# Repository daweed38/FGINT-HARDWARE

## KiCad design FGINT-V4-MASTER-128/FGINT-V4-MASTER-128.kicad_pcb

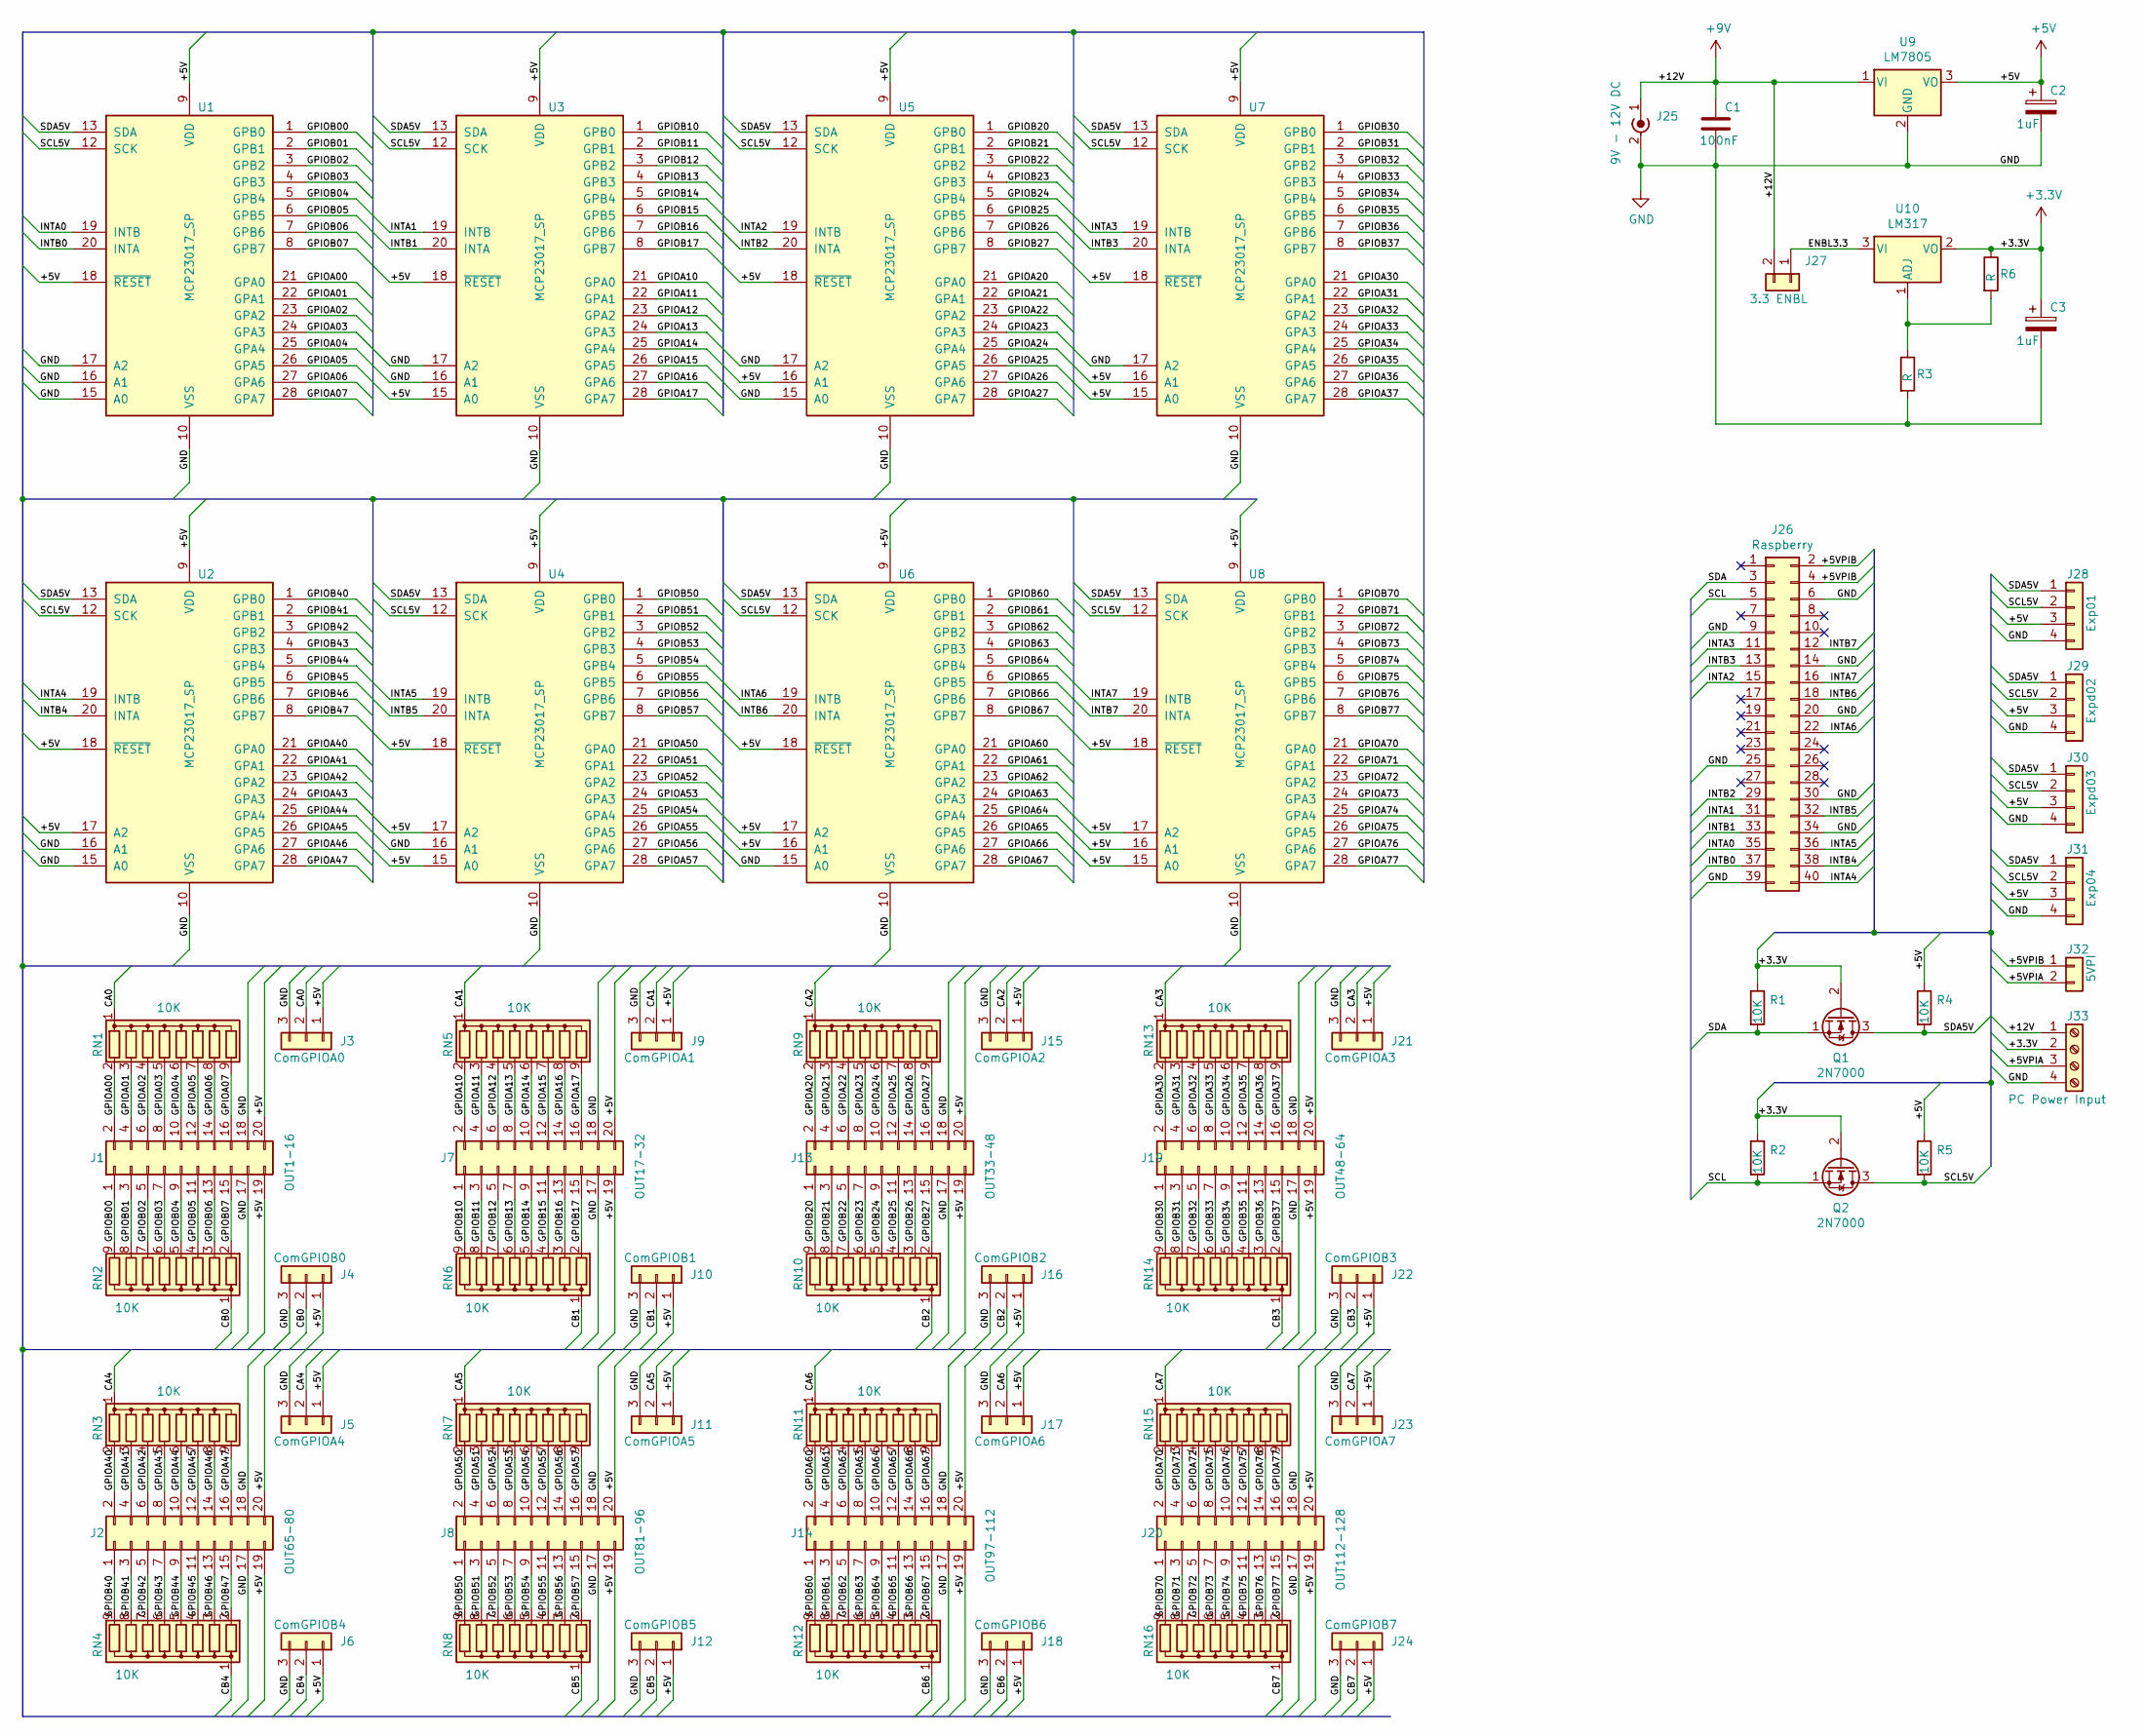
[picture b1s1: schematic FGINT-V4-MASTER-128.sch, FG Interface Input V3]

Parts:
C1: 100nF; C_Rect_L7.0mm_W2.5mm_P5.00mm
C2, C3: 1uF; CP_Radial_D5.0mm_P2.50mm
J1: OUT1-16; IDC-Header_2x10_P2.54mm_Horizontal
J2: OUT65-80; IDC-Header_2x10_P2.54mm_Horizontal
J3: ComGPIOA0; PinHeader_1x03_P2.54mm_Vertical
J4: ComGPIOB0; PinHeader_1x03_P2.54mm_Vertical
J5: ComGPIOA4; PinHeader_1x03_P2.54mm_Vertical
J6: ComGPIOB4; PinHeader_1x03_P2.54mm_Vertical
J7: OUT17-32; IDC-Header_2x10_P2.54mm_Horizontal
J8: OUT81-96; IDC-Header_2x10_P2.54mm_Horizontal
J9: ComGPIOA1; PinHeader_1x03_P2.54mm_Vertical
J10: ComGPIOB1; PinHeader_1x03_P2.54mm_Vertical
J11: ComGPIOA5; PinHeader_1x03_P2.54mm_Vertical
J12: ComGPIOB5; PinHeader_1x03_P2.54mm_Vertical
J13: OUT33-48; IDC-Header_2x10_P2.54mm_Horizontal
J14: OUT97-112; IDC-Header_2x10_P2.54mm_Horizontal
J15: ComGPIOA2; PinHeader_1x03_P2.54mm_Vertical
J16: ComGPIOB2; PinHeader_1x03_P2.54mm_Vertical
J17: ComGPIOA6; PinHeader_1x03_P2.54mm_Vertical
J18: ComGPIOB6; PinHeader_1x03_P2.54mm_Vertical
J19: OUT48-64; IDC-Header_2x10_P2.54mm_Horizontal
J20: OUT112-128; IDC-Header_2x10_P2.54mm_Horizontal
J21: ComGPIOA3; PinHeader_1x03_P2.54mm_Vertical
J22: ComGPIOB3; PinHeader_1x03_P2.54mm_Vertical
J23: ComGPIOA7; PinHeader_1x03_P2.54mm_Vertical
J24: ComGPIOB7; PinHeader_1x03_P2.54mm_Vertical
J25: 9V - 12V DC; BarrelJack_CUI_PJ-102AH_Horizontal
J26: Raspberry; IDC-Header_2x20_P2.54mm_Vertical
J27: 3.3 ENBL; PinHeader_1x02_P2.54mm_Vertical
J28: Exp01; Molex_KK-254_AE-6410-04A_1x04_P2.54mm_Vertical
J29: Expd02; Molex_KK-254_AE-6410-04A_1x04_P2.54mm_Vertical
J30: Expd03; Molex_KK-254_AE-6410-04A_1x04_P2.54mm_Vertical
J31: Exp04; Molex_KK-254_AE-6410-04A_1x04_P2.54mm_Vertical
J32: 5VPI; PinHeader_1x02_P2.54mm_Vertical
J33: PC Power Input; TerminalBlock_bornier-4_P5.08mm
Q1, Q2: 2N7000; TO-92_Inline
R1, R2, R4, R5: 10K; R_Axial_DIN0207_L6.3mm_D2.5mm_P7.62mm_Horizontal
R3, R6: R; R_Axial_DIN0207_L6.3mm_D2.5mm_P7.62mm_Horizontal
RN1, RN2, RN3, RN4, RN5, RN6, RN7, RN8, RN9, RN10, RN11, RN12, RN13, RN14, RN15, RN16: 10K; R_Array_SIP9
U1, U2, U3, U4, U5, U6, U7, U8: MCP23017_SP; DIP-28_W7.62mm
U9: LM7805; TO-220-3_Horizontal_TabDown
U10: LM317; TO-220-3_Horizontal_TabDown

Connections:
+3V3: C3.1, J33.2, Q1.2 (G), Q2.2 (G), R1.1, R2.1, R6.1, U10.2 (VO)
+5V: C2.1, J1.19, J1.20, J2.19, J2.20, J3.1, J4.1, J5.1, J6.1, J7.19, J7.20, J8.19, J8.20, J9.1, J10.1, J11.1, J12.1, J13.19, J13.20, J14.19, J14.20, J15.1, J16.1, J17.1, J18.1, J19.19, J19.20, J20.19, J20.20, J21.1, J22.1, J23.1, J24.1, J28.3, J29.3, J30.3, J31.3, R4.1, R5.1, U1.9 (VDD), U1.18 (~RESET~), U2.9 (VDD), U2.17 (A2), U2.18 (~RESET~), U3.9 (VDD), U3.15 (A0), U3.18 (~RESET~), U4.9 (VDD), U4.15 (A0), U4.17 (A2), U4.18 (~RESET~), U5.9 (VDD), U5.16 (A1), U5.18 (~RESET~), U6.9 (VDD), U6.16 (A1), U6.17 (A2), U6.18 (~RESET~), U7.9 (VDD), U7.15 (A0), U7.16 (A1), U7.18 (~RESET~), U8.9 (VDD), U8.15 (A0), U8.16 (A1), U8.17 (A2), U8.18 (~RESET~), U9.3 (VO)
+9V: C1.1, J25.1 (In), J27.2, J33.1, U9.1 (VI)
/+5VPIA: J32.2, J33.3
/+5VPIB: J26.2, J26.4, J32.1
/CA0: J3.2, RN1.1 (common)
/CA1: J9.2, RN5.1 (common)
/CA2: J15.2, RN9.1 (common)
/CA3: J21.2, RN13.1 (common)
/CA4: J5.2, RN3.1 (common)
/CA5: J11.2, RN7.1 (common)
/CA6: J17.2, RN11.1 (common)
/CA7: J23.2, RN15.1 (common)
/CB0: J4.2, RN2.1 (common)
/CB1: J10.2, RN6.1 (common)
/CB2: J16.2, RN10.1 (common)
/CB3: J22.2, RN14.1 (common)
/CB4: J6.2, RN4.1 (common)
/CB5: J12.2, RN8.1 (common)
/CB6: J18.2, RN12.1 (common)
/CB7: J24.2, RN16.1 (common)
/ENBL3.3: J27.1, U10.3 (VI)
/GPIOA00: J1.2, RN1.2 (R1), U1.21 (GPA0)
/GPIOA01: J1.4, RN1.3 (R2), U1.22 (GPA1)
/GPIOA02: J1.6, RN1.4 (R3), U1.23 (GPA2)
/GPIOA03: J1.8, RN1.5 (R4), U1.24 (GPA3)
/GPIOA04: J1.10, RN1.6 (R5), U1.25 (GPA4)
/GPIOA05: J1.12, RN1.7 (R6), U1.26 (GPA5)
/GPIOA06: J1.14, RN1.8 (R7), U1.27 (GPA6)
/GPIOA07: J1.16, RN1.9 (R8), U1.28 (GPA7)
/GPIOA10: J7.2, RN5.2 (R1), U3.21 (GPA0)
/GPIOA11: J7.4, RN5.3 (R2), U3.22 (GPA1)
/GPIOA12: J7.6, RN5.4 (R3), U3.23 (GPA2)
/GPIOA13: J7.8, RN5.5 (R4), U3.24 (GPA3)
/GPIOA14: J7.10, RN5.6 (R5), U3.25 (GPA4)
/GPIOA15: J7.12, RN5.7 (R6), U3.26 (GPA5)
/GPIOA16: J7.14, RN5.8 (R7), U3.27 (GPA6)
/GPIOA17: J7.16, RN5.9 (R8), U3.28 (GPA7)
/GPIOA20: J13.2, RN9.2 (R1), U5.21 (GPA0)
/GPIOA21: J13.4, RN9.3 (R2), U5.22 (GPA1)
/GPIOA22: J13.6, RN9.4 (R3), U5.23 (GPA2)
/GPIOA23: J13.8, RN9.5 (R4), U5.24 (GPA3)
/GPIOA24: J13.10, RN9.6 (R5), U5.25 (GPA4)
/GPIOA25: J13.12, RN9.7 (R6), U5.26 (GPA5)
/GPIOA26: J13.14, RN9.8 (R7), U5.27 (GPA6)
/GPIOA27: J13.16, RN9.9 (R8), U5.28 (GPA7)
/GPIOA30: J19.2, RN13.2 (R1), U7.21 (GPA0)
/GPIOA31: J19.4, RN13.3 (R2), U7.22 (GPA1)
/GPIOA32: J19.6, RN13.4 (R3), U7.23 (GPA2)
/GPIOA33: J19.8, RN13.5 (R4), U7.24 (GPA3)
/GPIOA34: J19.10, RN13.6 (R5), U7.25 (GPA4)
/GPIOA35: J19.12, RN13.7 (R6), U7.26 (GPA5)
/GPIOA36: J19.14, RN13.8 (R7), U7.27 (GPA6)
/GPIOA37: J19.16, RN13.9 (R8), U7.28 (GPA7)
/GPIOA40: J2.2, RN3.2 (R1), U2.21 (GPA0)
/GPIOA41: J2.4, RN3.3 (R2), U2.22 (GPA1)
/GPIOA42: J2.6, RN3.4 (R3), U2.23 (GPA2)
/GPIOA43: J2.8, RN3.5 (R4), U2.24 (GPA3)
/GPIOA44: J2.10, RN3.6 (R5), U2.25 (GPA4)
/GPIOA45: J2.12, RN3.7 (R6), U2.26 (GPA5)
/GPIOA46: J2.14, RN3.8 (R7), U2.27 (GPA6)
/GPIOA47: J2.16, RN3.9 (R8), U2.28 (GPA7)
/GPIOA50: J8.2, RN7.2 (R1), U4.21 (GPA0)
/GPIOA51: J8.4, RN7.3 (R2), U4.22 (GPA1)
/GPIOA52: J8.6, RN7.4 (R3), U4.23 (GPA2)
/GPIOA53: J8.8, RN7.5 (R4), U4.24 (GPA3)
/GPIOA54: J8.10, RN7.6 (R5), U4.25 (GPA4)
/GPIOA55: J8.12, RN7.7 (R6), U4.26 (GPA5)
/GPIOA56: J8.14, RN7.8 (R7), U4.27 (GPA6)
/GPIOA57: J8.16, RN7.9 (R8), U4.28 (GPA7)
/GPIOA60: J14.2, RN11.2 (R1), U6.21 (GPA0)
/GPIOA61: J14.4, RN11.3 (R2), U6.22 (GPA1)
/GPIOA62: J14.6, RN11.4 (R3), U6.23 (GPA2)
/GPIOA63: J14.8, RN11.5 (R4), U6.24 (GPA3)
/GPIOA64: J14.10, RN11.6 (R5), U6.25 (GPA4)
/GPIOA65: J14.12, RN11.7 (R6), U6.26 (GPA5)
/GPIOA66: J14.14, RN11.8 (R7), U6.27 (GPA6)
/GPIOA67: J14.16, RN11.9 (R8), U6.28 (GPA7)
/GPIOA70: J20.2, RN15.2 (R1), U8.21 (GPA0)
/GPIOA71: J20.4, RN15.3 (R2), U8.22 (GPA1)
/GPIOA72: J20.6, RN15.4 (R3), U8.23 (GPA2)
/GPIOA73: J20.8, RN15.5 (R4), U8.24 (GPA3)
/GPIOA74: J20.10, RN15.6 (R5), U8.25 (GPA4)
/GPIOA75: J20.12, RN15.7 (R6), U8.26 (GPA5)
/GPIOA76: J20.14, RN15.8 (R7), U8.27 (GPA6)
/GPIOA77: J20.16, RN15.9 (R8), U8.28 (GPA7)
/GPIOB00: J1.1, RN2.9 (R8), U1.1 (GPB0)
/GPIOB01: J1.3, RN2.8 (R7), U1.2 (GPB1)
/GPIOB02: J1.5, RN2.7 (R6), U1.3 (GPB2)
/GPIOB03: J1.7, RN2.6 (R5), U1.4 (GPB3)
/GPIOB04: J1.9, RN2.5 (R4), U1.5 (GPB4)
/GPIOB05: J1.11, RN2.4 (R3), U1.6 (GPB5)
/GPIOB06: J1.13, RN2.3 (R2), U1.7 (GPB6)
/GPIOB07: J1.15, RN2.2 (R1), U1.8 (GPB7)
/GPIOB10: J7.1, RN6.9 (R8), U3.1 (GPB0)
/GPIOB11: J7.3, RN6.8 (R7), U3.2 (GPB1)
/GPIOB12: J7.5, RN6.7 (R6), U3.3 (GPB2)
/GPIOB13: J7.7, RN6.6 (R5), U3.4 (GPB3)
/GPIOB14: J7.9, RN6.5 (R4), U3.5 (GPB4)
/GPIOB15: J7.11, RN6.4 (R3), U3.6 (GPB5)
/GPIOB16: J7.13, RN6.3 (R2), U3.7 (GPB6)
/GPIOB17: J7.15, RN6.2 (R1), U3.8 (GPB7)
/GPIOB20: J13.1, RN10.9 (R8), U5.1 (GPB0)
/GPIOB21: J13.3, RN10.8 (R7), U5.2 (GPB1)
/GPIOB22: J13.5, RN10.7 (R6), U5.3 (GPB2)
/GPIOB23: J13.7, RN10.6 (R5), U5.4 (GPB3)
/GPIOB24: J13.9, RN10.5 (R4), U5.5 (GPB4)
/GPIOB25: J13.11, RN10.4 (R3), U5.6 (GPB5)
/GPIOB26: J13.13, RN10.3 (R2), U5.7 (GPB6)
/GPIOB27: J13.15, RN10.2 (R1), U5.8 (GPB7)
/GPIOB30: J19.1, RN14.9 (R8), U7.1 (GPB0)
/GPIOB31: J19.3, RN14.8 (R7), U7.2 (GPB1)
/GPIOB32: J19.5, RN14.7 (R6), U7.3 (GPB2)
/GPIOB33: J19.7, RN14.6 (R5), U7.4 (GPB3)
/GPIOB34: J19.9, RN14.5 (R4), U7.5 (GPB4)
/GPIOB35: J19.11, RN14.4 (R3), U7.6 (GPB5)
/GPIOB36: J19.13, RN14.3 (R2), U7.7 (GPB6)
/GPIOB37: J19.15, RN14.2 (R1), U7.8 (GPB7)
/GPIOB40: J2.1, RN4.9 (R8), U2.1 (GPB0)
/GPIOB41: J2.3, RN4.8 (R7), U2.2 (GPB1)
/GPIOB42: J2.5, RN4.7 (R6), U2.3 (GPB2)
/GPIOB43: J2.7, RN4.6 (R5), U2.4 (GPB3)
/GPIOB44: J2.9, RN4.5 (R4), U2.5 (GPB4)
/GPIOB45: J2.11, RN4.4 (R3), U2.6 (GPB5)
/GPIOB46: J2.13, RN4.3 (R2), U2.7 (GPB6)
/GPIOB47: J2.15, RN4.2 (R1), U2.8 (GPB7)
/GPIOB50: J8.1, RN8.9 (R8), U4.1 (GPB0)
/GPIOB51: J8.3, RN8.8 (R7), U4.2 (GPB1)
/GPIOB52: J8.5, RN8.7 (R6), U4.3 (GPB2)
/GPIOB53: J8.7, RN8.6 (R5), U4.4 (GPB3)
/GPIOB54: J8.9, RN8.5 (R4), U4.5 (GPB4)
/GPIOB55: J8.11, RN8.4 (R3), U4.6 (GPB5)
/GPIOB56: J8.13, RN8.3 (R2), U4.7 (GPB6)
/GPIOB57: J8.15, RN8.2 (R1), U4.8 (GPB7)
/GPIOB60: J14.1, RN12.9 (R8), U6.1 (GPB0)
/GPIOB61: J14.3, RN12.8 (R7), U6.2 (GPB1)
/GPIOB62: J14.5, RN12.7 (R6), U6.3 (GPB2)
/GPIOB63: J14.7, RN12.6 (R5), U6.4 (GPB3)
/GPIOB64: J14.9, RN12.5 (R4), U6.5 (GPB4)
/GPIOB65: J14.11, RN12.4 (R3), U6.6 (GPB5)
/GPIOB66: J14.13, RN12.3 (R2), U6.7 (GPB6)
/GPIOB67: J14.15, RN12.2 (R1), U6.8 (GPB7)
/GPIOB70: J20.1, RN16.9 (R8), U8.1 (GPB0)
/GPIOB71: J20.3, RN16.8 (R7), U8.2 (GPB1)
/GPIOB72: J20.5, RN16.7 (R6), U8.3 (GPB2)
/GPIOB73: J20.7, RN16.6 (R5), U8.4 (GPB3)
/GPIOB74: J20.9, RN16.5 (R4), U8.5 (GPB4)
/GPIOB75: J20.11, RN16.4 (R3), U8.6 (GPB5)
/GPIOB76: J20.13, RN16.3 (R2), U8.7 (GPB6)
/GPIOB77: J20.15, RN16.2 (R1), U8.8 (GPB7)
/INTA0: J26.35, U1.19 (INTB)
/INTA1: J26.31, U3.19 (INTB)
/INTA2: J26.15, U5.19 (INTB)
/INTA3: J26.11, U7.19 (INTB)
/INTA4: J26.40, U2.19 (INTB)
/INTA5: J26.36, U4.19 (INTB)
/INTA6: J26.22, U6.19 (INTB)
/INTA7: J26.16, U8.19 (INTB)
/INTB0: J26.37, U1.20 (INTA)
/INTB1: J26.33, U3.20 (INTA)
/INTB2: J26.29, U5.20 (INTA)
/INTB3: J26.13, U7.20 (INTA)
/INTB4: J26.38, U2.20 (INTA)
/INTB5: J26.32, U4.20 (INTA)
/INTB6: J26.18, U6.20 (INTA)
/INTB7: J26.12, U8.20 (INTA)
/SCL: J26.5, Q2.1 (S), R2.2
/SCL5V: J28.2, J29.2, J30.2, J31.2, Q2.3 (D), R5.2, U1.12 (SCK), U2.12 (SCK), U3.12 (SCK), U4.12 (SCK), U5.12 (SCK), U6.12 (SCK), U7.12 (SCK), U8.12 (SCK)
/SDA: J26.3, Q1.1 (S), R1.2
/SDA5V: J28.1, J29.1, J30.1, J31.1, Q1.3 (D), R4.2, U1.13 (SDA), U2.13 (SDA), U3.13 (SDA), U4.13 (SDA), U5.13 (SDA), U6.13 (SDA), U7.13 (SDA), U8.13 (SDA)
GND: C1.2, C2.2, C3.2, J1.17, J1.18, J2.17, J2.18, J3.3, J4.3, J5.3, J6.3, J7.17, J7.18, J8.17, J8.18, J9.3, J10.3, J11.3, J12.3, J13.17, J13.18, J14.17, J14.18, J15.3, J16.3, J17.3, J18.3, J19.17, J19.18, J20.17, J20.18, J21.3, J22.3, J23.3, J24.3, J25.2 (Ext), J26.6, J26.9, J26.14, J26.20, J26.25, J26.30, J26.34, J26.39, J28.4, J29.4, J30.4, J31.4, J33.4, R3.2, U1.10 (VSS), U1.15 (A0), U1.16 (A1), U1.17 (A2), U2.10 (VSS), U2.15 (A0), U2.16 (A1), U3.10 (VSS), U3.16 (A1), U3.17 (A2), U4.10 (VSS), U4.16 (A1), U5.10 (VSS), U5.15 (A0), U5.17 (A2), U6.10 (VSS), U6.15 (A0), U7.10 (VSS), U7.17 (A2), U8.10 (VSS), U9.2 (GND)
unnamed: R3.1, R6.2, U10.1 (ADJ)

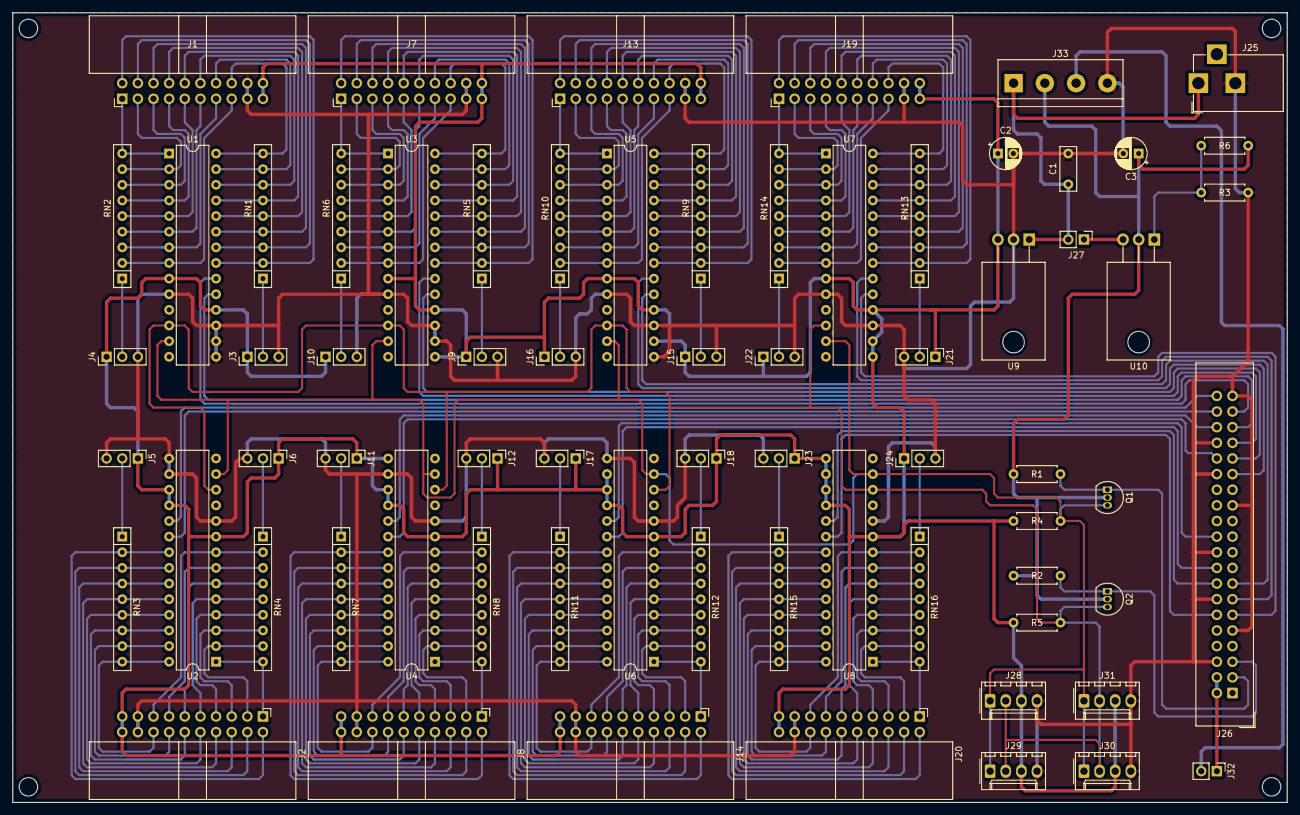
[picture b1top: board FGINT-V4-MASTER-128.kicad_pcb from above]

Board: 2 copper layers, 207.0 x 128.3 mm, 70 parts (0 on the bottom side), 172 nets.

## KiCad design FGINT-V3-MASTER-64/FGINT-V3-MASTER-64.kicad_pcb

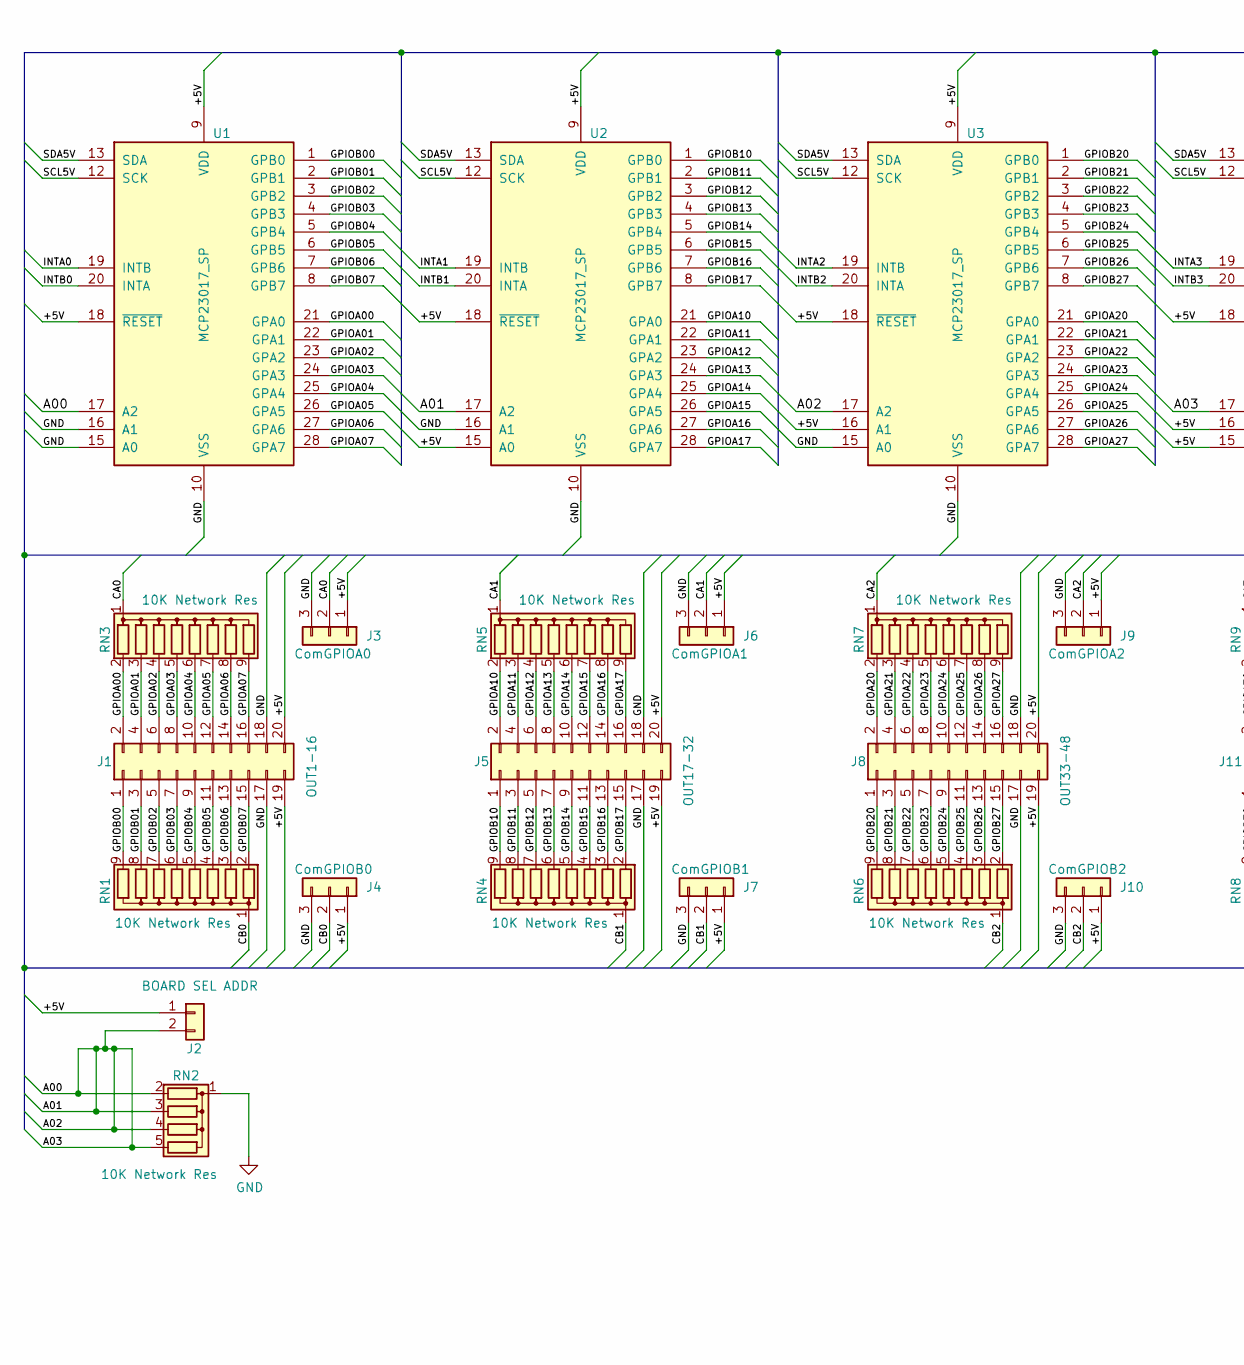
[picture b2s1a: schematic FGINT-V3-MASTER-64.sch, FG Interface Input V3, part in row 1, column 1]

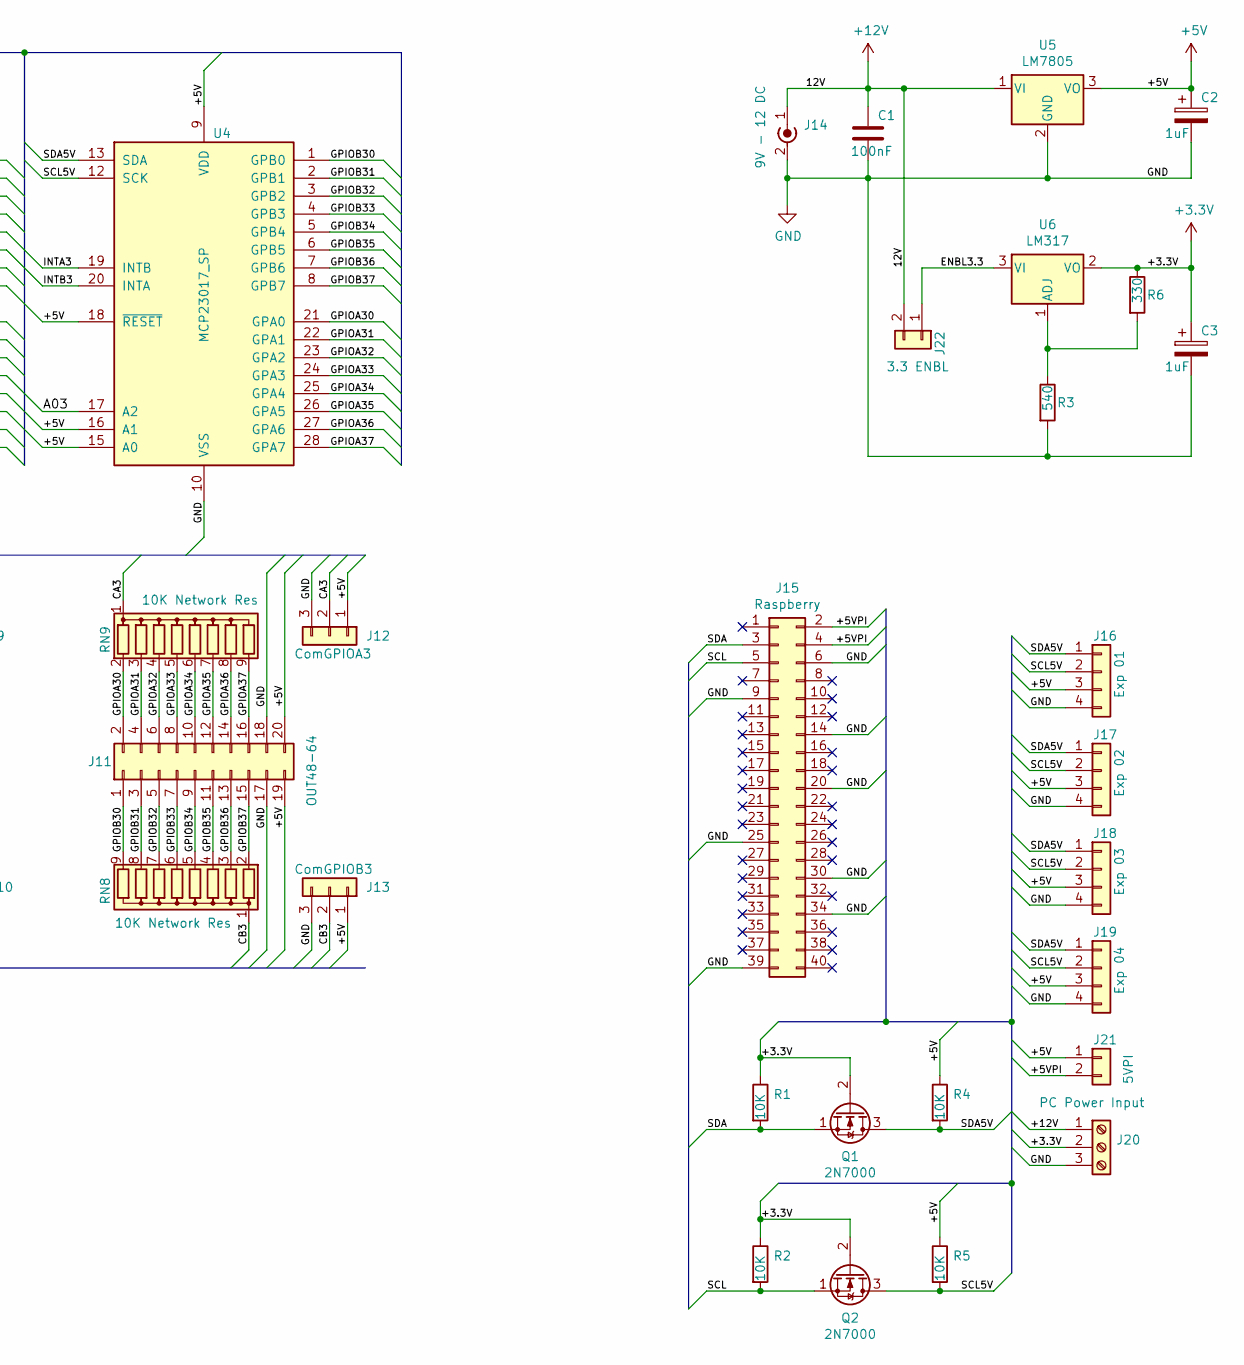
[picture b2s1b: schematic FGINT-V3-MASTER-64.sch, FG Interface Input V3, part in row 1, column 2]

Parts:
C1: 100nF; C_Rect_L7.0mm_W2.5mm_P5.00mm
C2, C3: 1uF; CP_Radial_D5.0mm_P2.50mm
J1: OUT1-16; IDC-Header_2x10_P2.54mm_Horizontal
J2: BOARD SEL ADDR; PinHeader_1x02_P2.54mm_Vertical
J3: ComGPIOA0; PinHeader_1x03_P2.54mm_Vertical
J4: ComGPIOB0; PinHeader_1x03_P2.54mm_Vertical
J5: OUT17-32; IDC-Header_2x10_P2.54mm_Horizontal
J6: ComGPIOA1; PinHeader_1x03_P2.54mm_Vertical
J7: ComGPIOB1; PinHeader_1x03_P2.54mm_Vertical
J8: OUT33-48; IDC-Header_2x10_P2.54mm_Horizontal
J9: ComGPIOA2; PinHeader_1x03_P2.54mm_Vertical
J10: ComGPIOB2; PinHeader_1x03_P2.54mm_Vertical
J11: OUT48-64; IDC-Header_2x10_P2.54mm_Horizontal
J12: ComGPIOA3; PinHeader_1x03_P2.54mm_Vertical
J13: ComGPIOB3; PinHeader_1x03_P2.54mm_Vertical
J14: 9V - 12 DC; BarrelJack_CUI_PJ-102AH_Horizontal
J15: Raspberry; IDC-Header_2x20_P2.54mm_Vertical
J16: Exp 01; Molex_KK-254_AE-6410-04A_1x04_P2.54mm_Vertical
J17: Exp 02; Molex_KK-254_AE-6410-04A_1x04_P2.54mm_Vertical
J18: Exp 03; Molex_KK-254_AE-6410-04A_1x04_P2.54mm_Vertical
J19: Exp 04; Molex_KK-254_AE-6410-04A_1x04_P2.54mm_Vertical
J20: PC Power Input; TerminalBlock_bornier-3_P5.08mm
J21: 5VPI; PinHeader_1x02_P2.54mm_Vertical
J22: 3.3 ENBL; PinHeader_1x02_P2.54mm_Vertical
Q1, Q2: 2N7000; TO-92L_Inline_Wide
R1, R2, R4, R5: 10K; R_Axial_DIN0207_L6.3mm_D2.5mm_P7.62mm_Horizontal
R3: 540; R_Axial_DIN0207_L6.3mm_D2.5mm_P7.62mm_Horizontal
R6: 330; R_Axial_DIN0207_L6.3mm_D2.5mm_P7.62mm_Horizontal
RN1, RN3, RN4, RN5, RN6, RN7, RN8, RN9: 10K Network Res; R_Array_SIP9
RN2: 10K Network Res; R_Array_SIP5
U1, U2, U3, U4: MCP23017_SP; DIP-28_W7.62mm
U5: LM7805; TO-220-3_Horizontal_TabDown
U6: LM317; TO-220-3_Horizontal_TabDown

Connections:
+3V3: C3.1, J20.2, Q1.2 (G), Q2.2 (G), R1.1, R2.1, R6.1, U6.2 (VO)
+5V: C2.1, J1.19, J1.20, J2.1, J3.1, J4.1, J5.19, J5.20, J6.1, J7.1, J8.19, J8.20, J9.1, J10.1, J11.19, J11.20, J12.1, J13.1, J16.3, J17.3, J18.3, J19.3, J21.1, R4.1, R5.1, U1.9 (VDD), U1.18 (~RESET~), U2.9 (VDD), U2.15 (A0), U2.18 (~RESET~), U3.9 (VDD), U3.16 (A1), U3.18 (~RESET~), U4.9 (VDD), U4.15 (A0), U4.16 (A1), U4.18 (~RESET~), U5.3 (VO)
+12V: C1.1, J14.1 (In), J20.1, J22.2, U5.1 (VI)
/+5VPI: J15.2, J15.4, J21.2
/A00: J2.2, RN2.2 (R1), RN2.3 (R2), RN2.4 (R3), RN2.5 (R4), U1.17 (A2), U2.17 (A2), U3.17 (A2), U4.17 (A2)
/CA0: J3.2, RN3.1 (common)
/CA1: J6.2, RN5.1 (common)
/CA2: J9.2, RN7.1 (common)
/CA3: J12.2, RN9.1 (common)
/CB0: J4.2, RN1.1 (common)
/CB1: J7.2, RN4.1 (common)
/CB2: J10.2, RN6.1 (common)
/CB3: J13.2, RN8.1 (common)
/ENBL3.3: J22.1, U6.3 (VI)
/GPIOA00: J1.2, RN3.2 (R1), U1.21 (GPA0)
/GPIOA01: J1.4, RN3.3 (R2), U1.22 (GPA1)
/GPIOA02: J1.6, RN3.4 (R3), U1.23 (GPA2)
/GPIOA03: J1.8, RN3.5 (R4), U1.24 (GPA3)
/GPIOA04: J1.10, RN3.6 (R5), U1.25 (GPA4)
/GPIOA05: J1.12, RN3.7 (R6), U1.26 (GPA5)
/GPIOA06: J1.14, RN3.8 (R7), U1.27 (GPA6)
/GPIOA07: J1.16, RN3.9 (R8), U1.28 (GPA7)
/GPIOA10: J5.2, RN5.2 (R1), U2.21 (GPA0)
/GPIOA11: J5.4, RN5.3 (R2), U2.22 (GPA1)
/GPIOA12: J5.6, RN5.4 (R3), U2.23 (GPA2)
/GPIOA13: J5.8, RN5.5 (R4), U2.24 (GPA3)
/GPIOA14: J5.10, RN5.6 (R5), U2.25 (GPA4)
/GPIOA15: J5.12, RN5.7 (R6), U2.26 (GPA5)
/GPIOA16: J5.14, RN5.8 (R7), U2.27 (GPA6)
/GPIOA17: J5.16, RN5.9 (R8), U2.28 (GPA7)
/GPIOA20: J8.2, RN7.2 (R1), U3.21 (GPA0)
/GPIOA21: J8.4, RN7.3 (R2), U3.22 (GPA1)
/GPIOA22: J8.6, RN7.4 (R3), U3.23 (GPA2)
/GPIOA23: J8.8, RN7.5 (R4), U3.24 (GPA3)
/GPIOA24: J8.10, RN7.6 (R5), U3.25 (GPA4)
/GPIOA25: J8.12, RN7.7 (R6), U3.26 (GPA5)
/GPIOA26: J8.14, RN7.8 (R7), U3.27 (GPA6)
/GPIOA27: J8.16, RN7.9 (R8), U3.28 (GPA7)
/GPIOA30: J11.2, RN9.2 (R1), U4.21 (GPA0)
/GPIOA31: J11.4, RN9.3 (R2), U4.22 (GPA1)
/GPIOA32: J11.6, RN9.4 (R3), U4.23 (GPA2)
/GPIOA33: J11.8, RN9.5 (R4), U4.24 (GPA3)
/GPIOA34: J11.10, RN9.6 (R5), U4.25 (GPA4)
/GPIOA35: J11.12, RN9.7 (R6), U4.26 (GPA5)
/GPIOA36: J11.14, RN9.8 (R7), U4.27 (GPA6)
/GPIOA37: J11.16, RN9.9 (R8), U4.28 (GPA7)
/GPIOB00: J1.1, RN1.9 (R8), U1.1 (GPB0)
/GPIOB01: J1.3, RN1.8 (R7), U1.2 (GPB1)
/GPIOB02: J1.5, RN1.7 (R6), U1.3 (GPB2)
/GPIOB03: J1.7, RN1.6 (R5), U1.4 (GPB3)
/GPIOB04: J1.9, RN1.5 (R4), U1.5 (GPB4)
/GPIOB05: J1.11, RN1.4 (R3), U1.6 (GPB5)
/GPIOB06: J1.13, RN1.3 (R2), U1.7 (GPB6)
/GPIOB07: J1.15, RN1.2 (R1), U1.8 (GPB7)
/GPIOB10: J5.1, RN4.9 (R8), U2.1 (GPB0)
/GPIOB11: J5.3, RN4.8 (R7), U2.2 (GPB1)
/GPIOB12: J5.5, RN4.7 (R6), U2.3 (GPB2)
/GPIOB13: J5.7, RN4.6 (R5), U2.4 (GPB3)
/GPIOB14: J5.9, RN4.5 (R4), U2.5 (GPB4)
/GPIOB15: J5.11, RN4.4 (R3), U2.6 (GPB5)
/GPIOB16: J5.13, RN4.3 (R2), U2.7 (GPB6)
/GPIOB17: J5.15, RN4.2 (R1), U2.8 (GPB7)
/GPIOB20: J8.1, RN6.9 (R8), U3.1 (GPB0)
/GPIOB21: J8.3, RN6.8 (R7), U3.2 (GPB1)
/GPIOB22: J8.5, RN6.7 (R6), U3.3 (GPB2)
/GPIOB23: J8.7, RN6.6 (R5), U3.4 (GPB3)
/GPIOB24: J8.9, RN6.5 (R4), U3.5 (GPB4)
/GPIOB25: J8.11, RN6.4 (R3), U3.6 (GPB5)
/GPIOB26: J8.13, RN6.3 (R2), U3.7 (GPB6)
/GPIOB27: J8.15, RN6.2 (R1), U3.8 (GPB7)
/GPIOB30: J11.1, RN8.9 (R8), U4.1 (GPB0)
/GPIOB31: J11.3, RN8.8 (R7), U4.2 (GPB1)
/GPIOB32: J11.5, RN8.7 (R6), U4.3 (GPB2)
/GPIOB33: J11.7, RN8.6 (R5), U4.4 (GPB3)
/GPIOB34: J11.9, RN8.5 (R4), U4.5 (GPB4)
/GPIOB35: J11.11, RN8.4 (R3), U4.6 (GPB5)
/GPIOB36: J11.13, RN8.3 (R2), U4.7 (GPB6)
/GPIOB37: J11.15, RN8.2 (R1), U4.8 (GPB7)
/INTA0: U1.19 (INTB)
/INTA1: U2.19 (INTB)
/INTA2: U3.19 (INTB)
/INTA3: U4.19 (INTB)
/INTB0: U1.20 (INTA)
/INTB1: U2.20 (INTA)
/INTB2: U3.20 (INTA)
/INTB3: U4.20 (INTA)
/SCL: J15.5, Q2.1 (S), R2.2
/SCL5V: J16.2, J17.2, J18.2, J19.2, Q2.3 (D), R5.2, U1.12 (SCK), U2.12 (SCK), U3.12 (SCK), U4.12 (SCK)
/SDA: J15.3, Q1.1 (S), R1.2
/SDA5V: J16.1, J17.1, J18.1, J19.1, Q1.3 (D), R4.2, U1.13 (SDA), U2.13 (SDA), U3.13 (SDA), U4.13 (SDA)
GND: C1.2, C2.2, C3.2, J1.17, J1.18, J3.3, J4.3, J5.17, J5.18, J6.3, J7.3, J8.17, J8.18, J9.3, J10.3, J11.17, J11.18, J12.3, J13.3, J14.2 (Ext), J15.6, J15.9, J15.14, J15.20, J15.25, J15.30, J15.34, J15.39, J16.4, J17.4, J18.4, J19.4, J20.3, R3.2, RN2.1 (common), U1.10 (VSS), U1.15 (A0), U1.16 (A1), U2.10 (VSS), U2.16 (A1), U3.10 (VSS), U3.15 (A0), U4.10 (VSS), U5.2 (GND)
unnamed: R3.1, R6.2, U6.1 (ADJ)

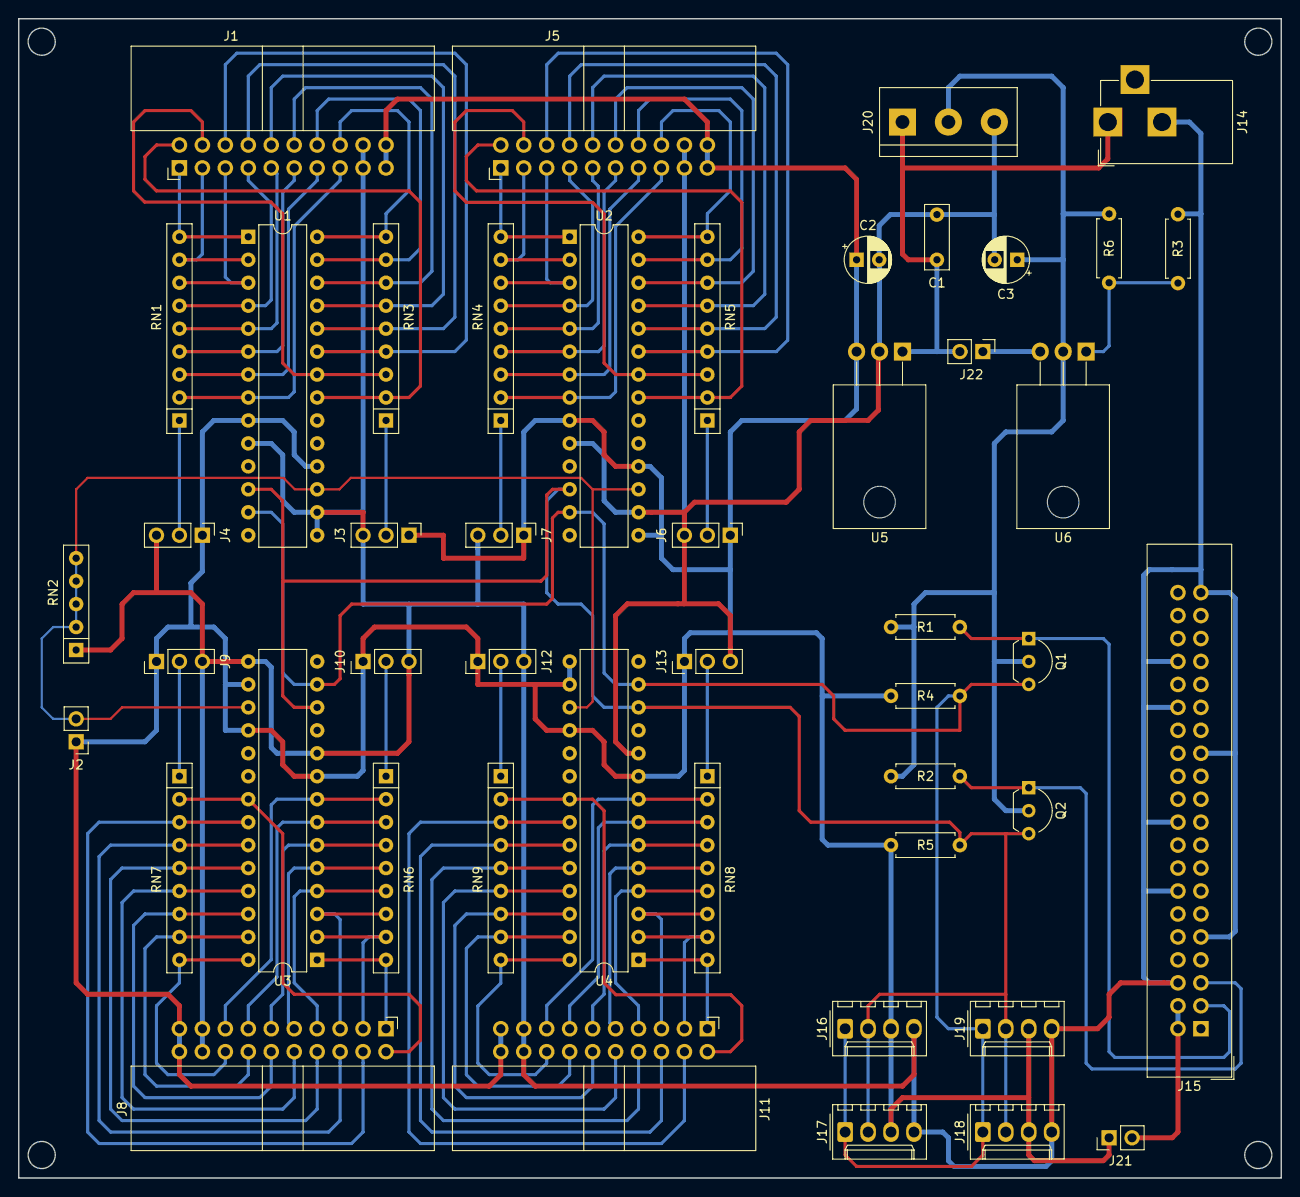
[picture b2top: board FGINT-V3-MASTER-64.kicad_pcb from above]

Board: 2 copper layers, 139.7 x 128.3 mm, 48 parts (0 on the bottom side), 84 nets.

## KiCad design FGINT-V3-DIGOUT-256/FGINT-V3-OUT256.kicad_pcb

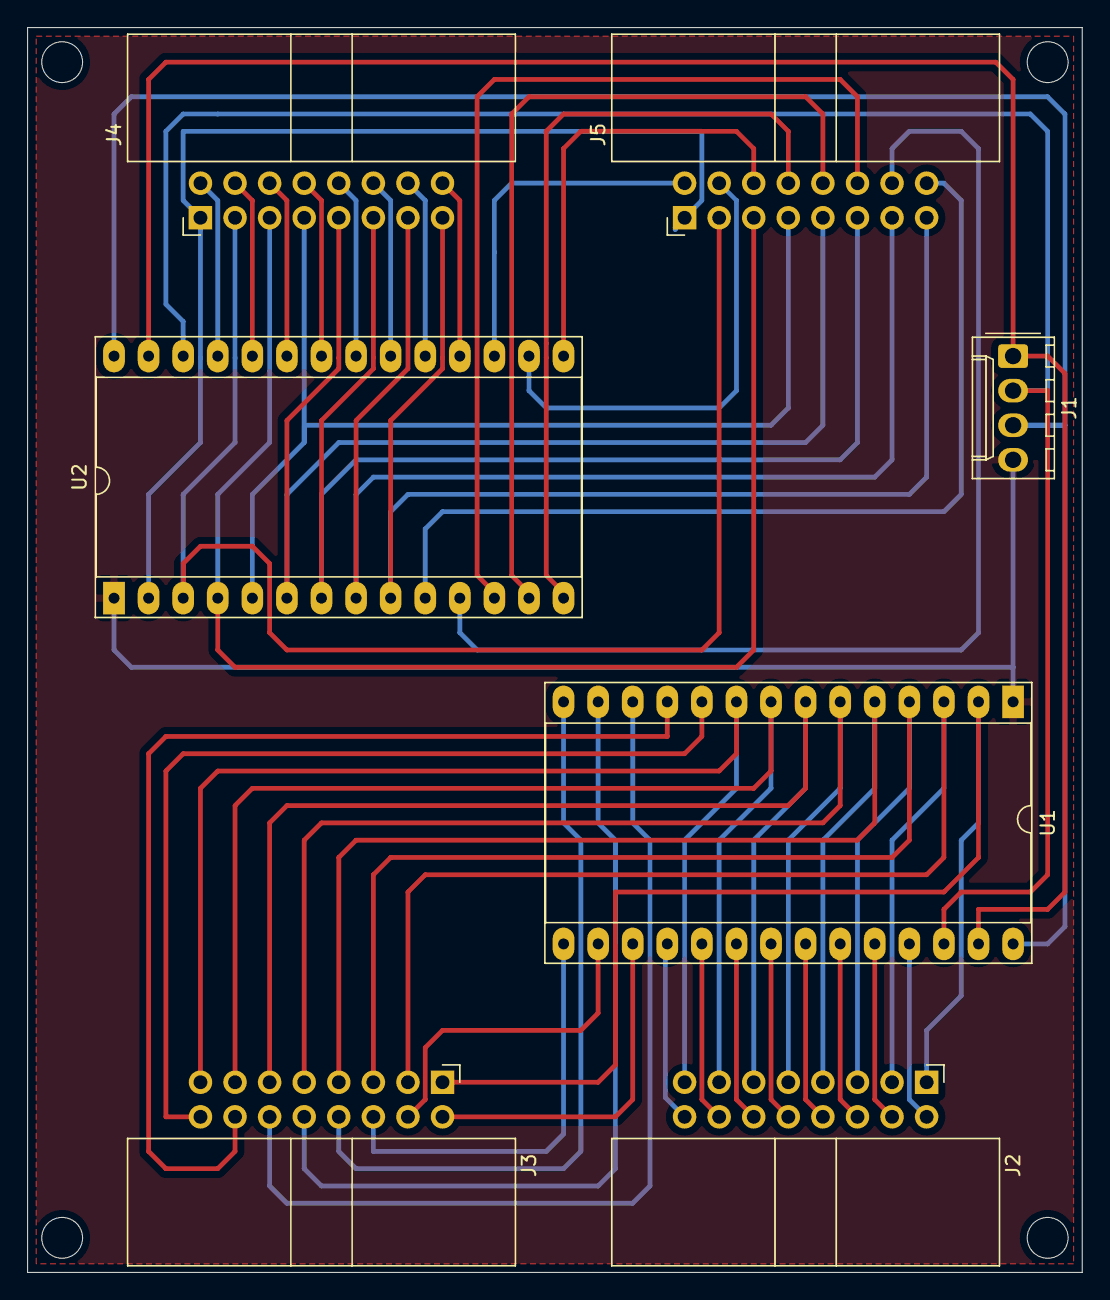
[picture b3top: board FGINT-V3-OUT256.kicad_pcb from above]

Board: 2 copper layers, 77.5 x 91.4 mm, 7 parts (0 on the bottom side), 52 nets.

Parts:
J1: MasterCon; Molex_KK-254_AE-6410-04A_1x04_P2.54mm_Vertical
J2, J3, J4, J5: Conn_02x08_Odd_Even; IDC-Header_2x08_P2.54mm_Horizontal
U1, U2: HT16K33_BREAKOUT; HT16K33_Breakout

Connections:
/+5V: J1.3, U1.28, U2.28
/COM00: J2.1, J3.1, U1.2
/COM01: J2.3, J3.3, U1.3
/COM02: J2.5, J3.5, U1.4
/COM03: J2.7, J3.7, U1.5
/COM04: J2.9, J3.9, U1.6
/COM05: J2.11, J3.11, U1.7
/COM06: J2.13, J3.13, U1.8
/COM07: J2.15, J3.15, U1.9
/COM10: J4.1, J5.1, U2.2
/COM11: J4.3, J5.3, U2.3
/COM12: J4.5, J5.5, U2.4
/COM13: J4.7, J5.7, U2.5
/COM14: J4.9, J5.9, U2.6
/COM15: J4.11, J5.11, U2.7
/COM16: J4.13, J5.13, U2.8
/COM17: J4.15, J5.15, U2.9
/GND: J1.4, U1.1, U2.1
/OUTA00: J2.2, U1.25
/OUTA01: J2.4, U1.24
/OUTA02: J2.6, U1.23
/OUTA03: J2.8, U1.22
/OUTA04: J2.10, U1.21
/OUTA05: J2.12, U1.20
/OUTA06: J2.14, U1.19
/OUTA07: J2.16, U1.18
/OUTA10: J4.2, U2.25
/OUTA11: J4.4, U2.24
/OUTA12: J4.6, U2.23
/OUTA13: J4.8, U2.22
/OUTA14: J4.10, U2.21
/OUTA15: J4.12, U2.20
/OUTA16: J4.14, U2.19
/OUTA17: J4.16, U2.18
/OUTB00: J3.2, U1.17
/OUTB01: J3.4, U1.16
/OUTB02: J3.6, U1.15
/OUTB03: J3.8, U1.14
/OUTB04: J3.10, U1.13
/OUTB05: J3.12, U1.12
/OUTB06: J3.14, U1.11
/OUTB07: J3.16, U1.10
/OUTB10: J5.2, U2.17
/OUTB11: J5.4, U2.16
/OUTB12: J5.6, U2.15
/OUTB13: J5.8, U2.14
/OUTB14: J5.10, U2.13
/OUTB15: J5.12, U2.12
/OUTB16: J5.14, U2.11
/OUTB17: J5.16, U2.10
/SCL5V: J1.2, U1.26, U2.26
/SDA5V: J1.1, U1.27, U2.27

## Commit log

2020-10-14 Initial Commit - Adding FGINT-V3-MASTER-64 - Master Interface - 64 I/O
2020-12-15 Adding 256 Digital Output Display Board
2020-12-15 Digit Ouput Board Folder Name Correction
2020-12-15 Removing old Digital Output Folder
2020-12-17 Adding Master Board 128 digital I/0 V3
2020-12-17 Renaming 128 I/O V3 to V4
2020-12-21 Update Power with +12V on Screw header
